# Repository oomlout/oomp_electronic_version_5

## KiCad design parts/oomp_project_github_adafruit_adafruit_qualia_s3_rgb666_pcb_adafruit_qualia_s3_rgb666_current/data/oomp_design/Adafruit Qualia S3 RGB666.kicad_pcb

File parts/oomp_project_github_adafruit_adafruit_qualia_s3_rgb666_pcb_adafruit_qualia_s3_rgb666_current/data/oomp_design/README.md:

# OOMP KiCad design copy

Open `Adafruit Qualia S3 RGB666.kicad_pro` (or the `.kicad_pcb` / `.kicad_sch`) in KiCad. Local OOMP libraries are under `libraries/`. Original inputs are preserved in [../original/](../original/).

Only verified unchanged installed KiCad defaults were renamed. Modified, custom, unmatched and unavailable items remain unchanged. Soldering variants are never swapped during conversion. Existing pad coordinates, nets and UUIDs are preserved.

See [conversion_report.yaml](conversion_report.yaml) for every conversion and skip. Copy this directory before editing; regeneration refuses to overwrite edited design files.

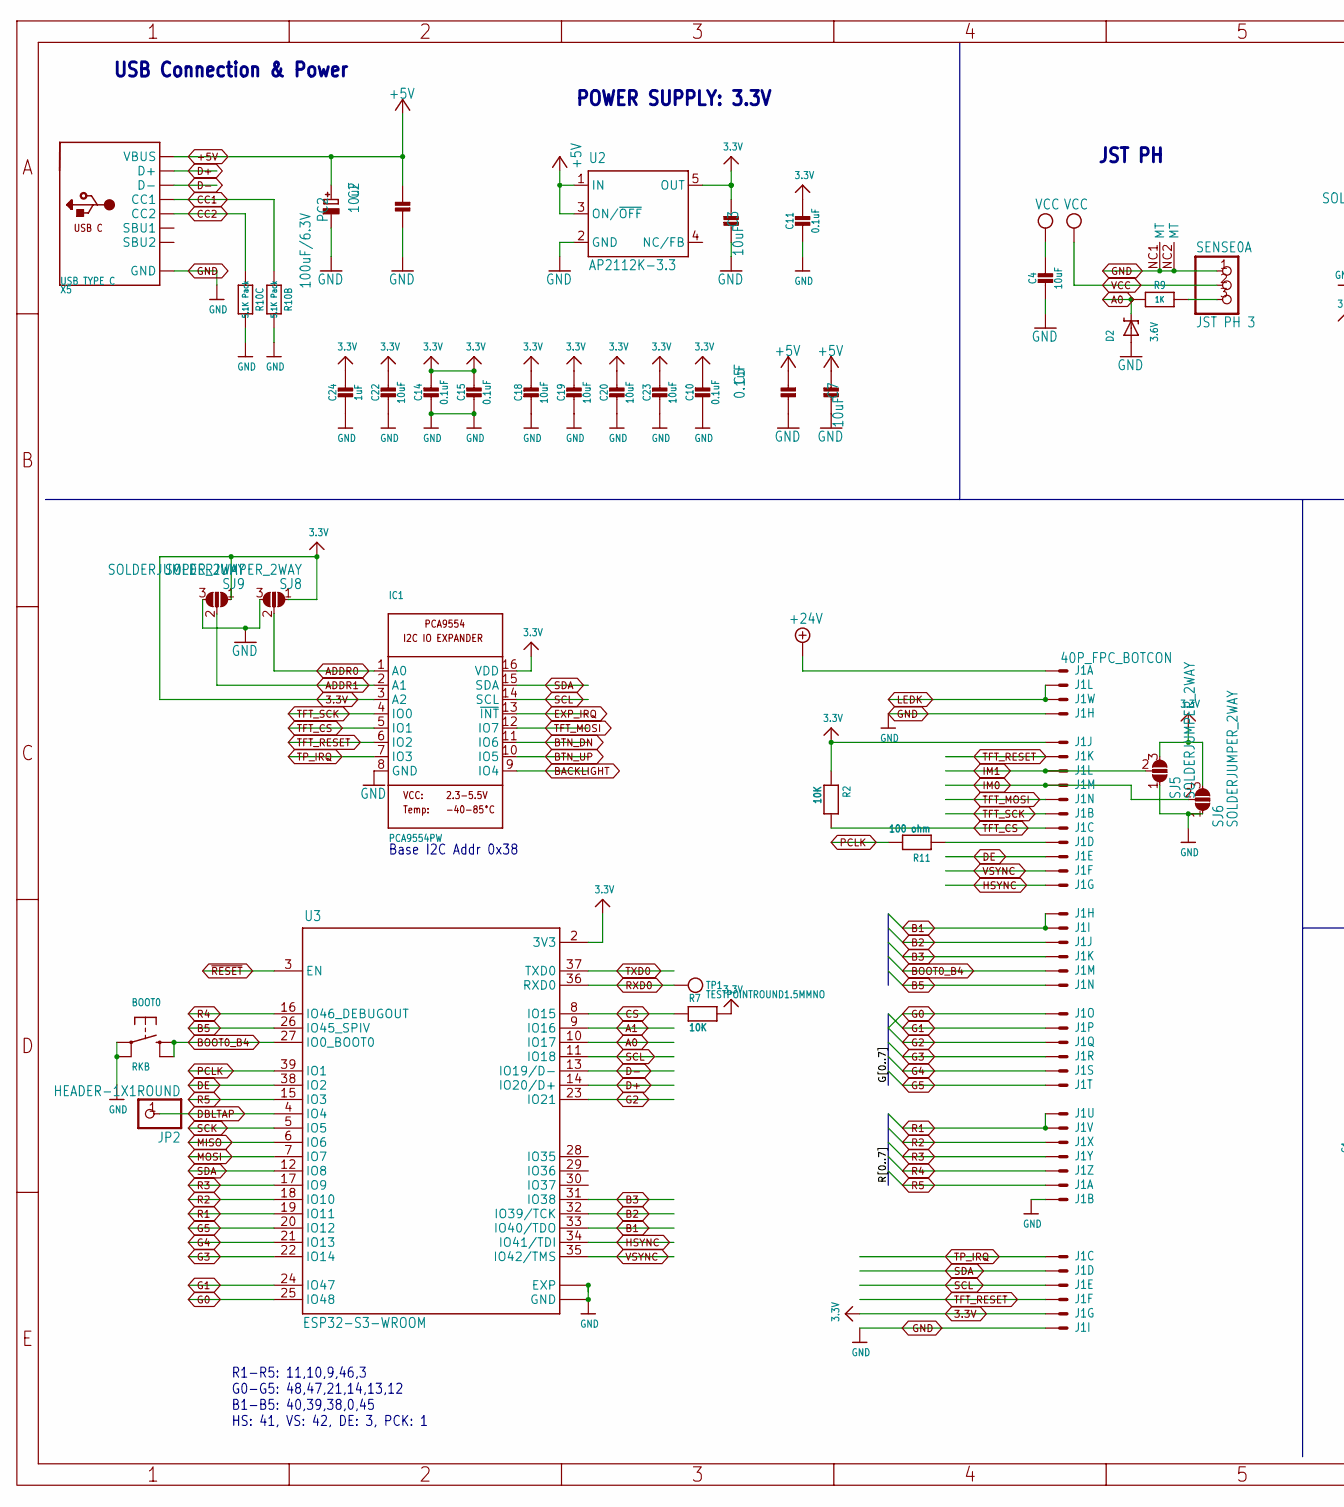
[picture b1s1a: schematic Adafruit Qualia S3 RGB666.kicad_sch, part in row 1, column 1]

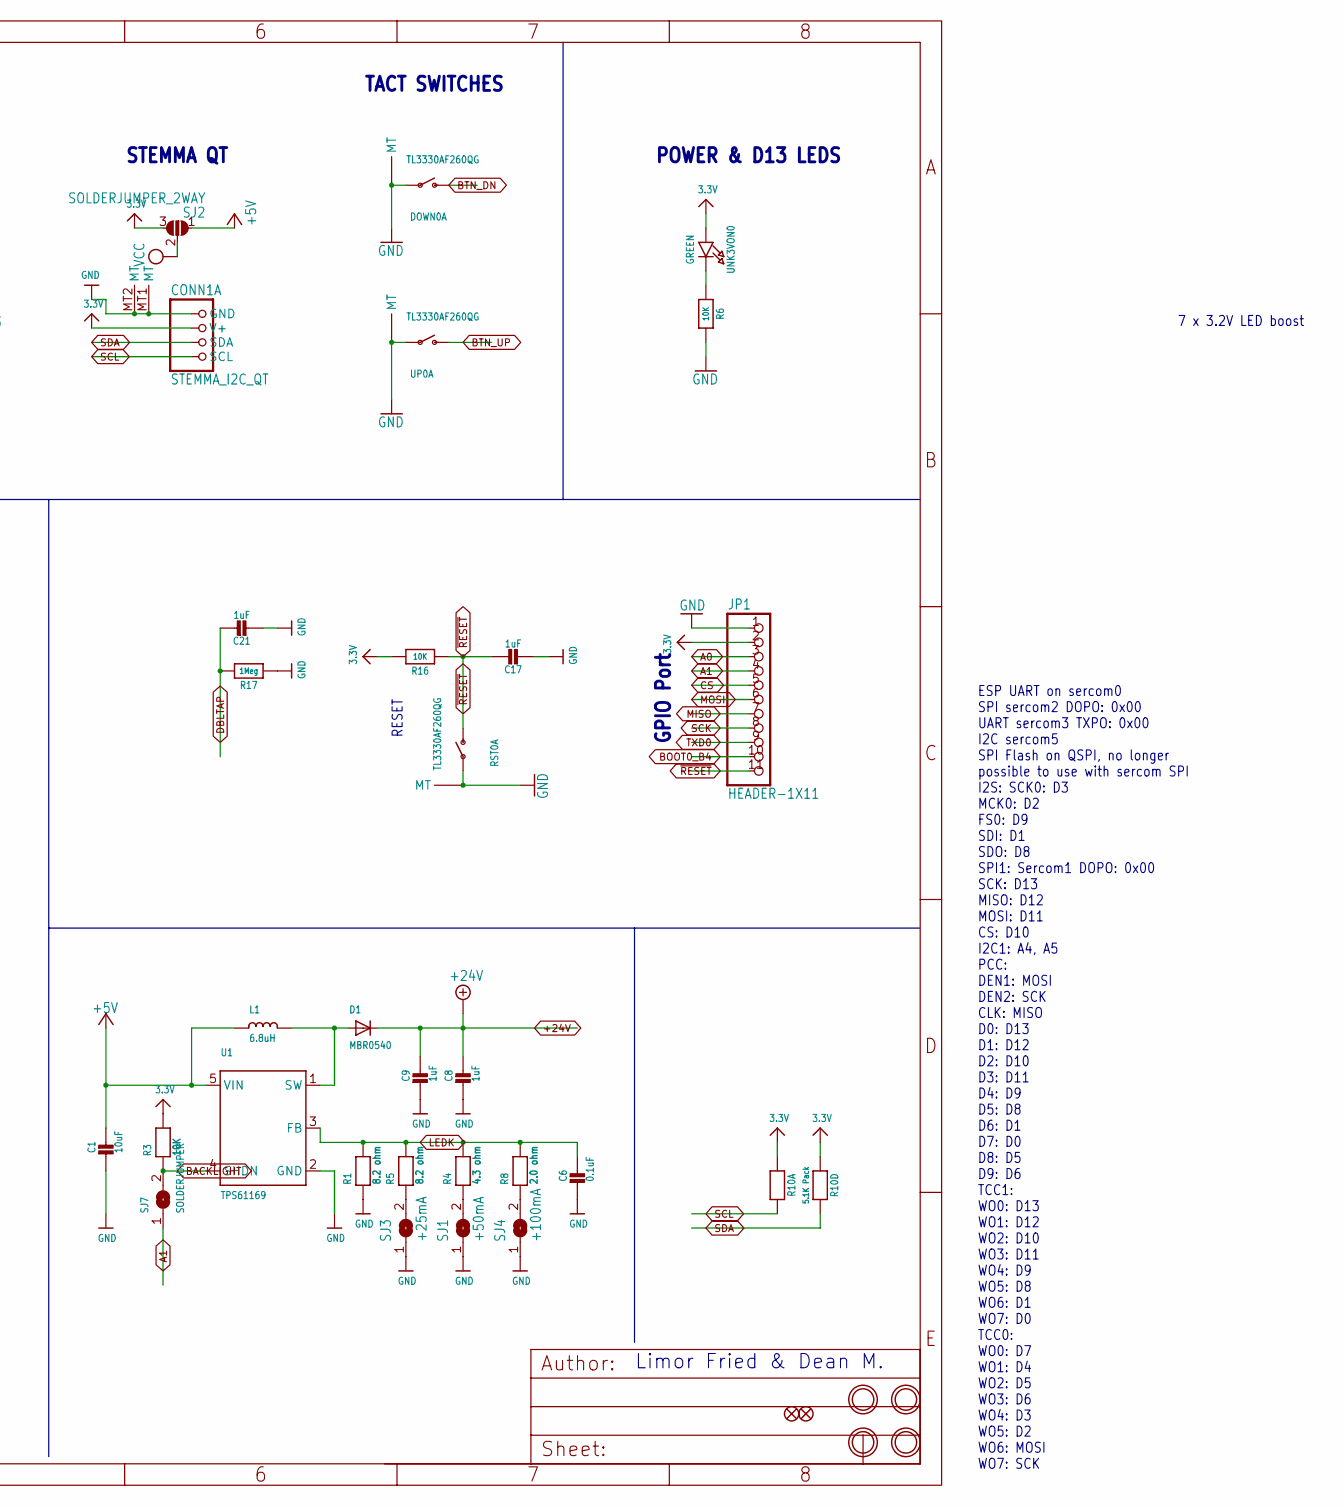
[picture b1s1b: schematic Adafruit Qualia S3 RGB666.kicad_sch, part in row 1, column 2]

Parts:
BOOT0: RKB; BTN_RKB2_4.6X2.8
C1, C2, C3, C4, C7, C18, C19, C20, C22, C23: 10uF; 0805-NO
C5, C6, C10, C11, C14, C15: 0.1uF; 0603-NO
C8, C9, C17, C21, C24: 1uF; 0603-NO
CONN1: STEMMA_I2C_QT; JST_SH4; LCSC C2845363
D1: MBR0540; SOD-123
D2: 3.6V; SOD-323
DOWN0: TL3330AF260QG; SPST_TACTILE_RA; LCSC C778159
FID1, FID2: FIDUCIAL_1MM
IC1: PCA9554PW; TSSOP16
J1: 40P_FPC_BOTCON; FPC_40
JP1: HEADER-1X11; 1X11_ROUND
JP2: HEADER-1X1ROUND; 1X01_ROUND
L1: 6.8uH; INDUCTOR_5X5MM_NR5040_NOTHERMALS
PC2: 100uF/6.3V; PANASONIC_D
R1, R5: 8.2 ohm; 0603-NO
R2, R3, R6, R7, R16: 10K; 0603-NO
R4: 4.3 ohm; 0603-NO
R8: 2.0 ohm; 0603-NO
R9: 1K; 0603-NO
R10: 5.1K Pack; RESPACK_4X0603
R11: 100 ohm; 0603-NO
R17: 1Meg; 0603-NO
RST0: TL3330AF260QG; SPST_TACTILE_RA; LCSC C778159
SENSE0: JST PH 3; JSTPH3
SJ1: +50mA; SOLDERJUMPER_ARROW_NOPASTE
SJ2, SJ5, SJ6, SJ8, SJ9: SOLDERJUMPER_2WAY; SOLDERJUMPER_2WAY_OPEN_NOPASTE
SJ3: +25mA; SOLDERJUMPER_ARROW_NOPASTE
SJ4: +100mA; SOLDERJUMPER_ARROW_NOPASTE
SJ7: SOLDERJUMPER; SOLDERJUMPER_ARROW_NOPASTE
TP1: TESTPOINTROUND1.5MMNO; TESTPOINT_ROUND_1.5MM_NO
U1: TPS61169; SC70-5
U2: AP2112K-3.3; SOT23-DBV
U3: ESP32-S3-WROOM; S3-WROOM32
U$14, U$19, U$22, U$24: MOUNTINGHOLE2.5; MOUNTINGHOLE_2.5_PLATED
UNK3VON0: GREEN; CHIPLED_0603_NOOUTLINE
UP0: TL3330AF260QG; SPST_TACTILE_RA; LCSC C778159
X5: USB TYPE C; USB_C_CUSB31-CFM2AX-01-X; LCSC C165948

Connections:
3.3V: C3.2, C10.2, C11.2, C14.2, C15.2, C18.1, C19.1, C20.1, C22.1, C23.1, C24.1, CONN1.2 (V+), IC1.3 (A2), IC1.16 (VDD), J1.5 (MS), J1.39 (MS), JP1.2, R2.1, R3.2, R7.2, R10.1, R10.4 (1), R16.2, SJ2.3, SJ5.3, SJ6.3, SJ8.1, SJ9.1, U2.5 (OUT), U3.2 (3V3), UNK3VON0.A
+5V: C1.1, C2.2, C5.2, C7.2, L1.P$1 (1), PC2.+, SJ2.1, U1.5 (VIN), U2.1 (IN), U2.3 (ON/~OFF), X5.A4B9 (VBUS), X5.B4A9 (VBUS)
+24V: C8.1, C9.1, D1.C, J1.1 (MSV)
A0: D2.C, JP1.3, R9.2, U3.10 (IO17)
A0_JST: R9.1, SENSE0.3
A1: JP1.4, SJ7.1, U3.9 (IO16)
ADDR0: IC1.1 (A0), SJ8.2
ADDR1: IC1.2 (A1), SJ9.2
B1: J1.16 (MS), J1.17 (MS), U3.33 (IO40/TDO)
B2: J1.18 (MS), U3.32 (IO39/TCK)
B3: J1.19 (MS), U3.31 (IO38)
B5: J1.21 (MS), U3.26 (IO45_SPIV)
BACKLIGHT: IC1.9 (IO4), R3.1, SJ7.2, U1.4 (SHDN)
BOOT0_B4: BOOT0.B (S), BOOT0.B' (S1), J1.20 (MS), JP1.10, U3.27 (IO0_BOOT0)
BTN_DN: DOWN0.2 (S), IC1.11 (IO6)
BTN_UP: IC1.10 (IO5), UP0.2 (S)
CC1: R10.2 (1), X5.A5 (CC1)
CC2: R10.3 (1), X5.B5 (CC2)
CS: JP1.5, R7.1, U3.8 (IO15)
D+: U3.14 (IO20/D+), X5.A6 (D+), X5.B6 (D+)
D-: U3.13 (IO19/D-), X5.A7 (D-), X5.B7 (D-)
DBLTAP: C21.1, JP2.1, R17.2, U3.4 (IO4)
DE: J1.13 (MS), U3.38 (IO2)
EXP_IRQ: IC1.13 (~INT)
G0: J1.22 (MS), U3.25 (IO48)
G1: J1.23 (MS), U3.24 (IO47)
G2: J1.24 (MS), U3.23 (IO21)
G3: J1.25 (MS), U3.22 (IO14)
G4: J1.26 (MS), U3.21 (IO13)
G5: J1.27 (MS), U3.20 (IO12)
GND: BOOT0.A, BOOT0.A' (P1), C1.2, C2.1, C3.1, C4.2, C5.1, C6.2, C7.1, C8.2, C9.2, C10.1, C11.1, C14.1, C15.1, C17.2, C18.2, C19.2, C20.2, C21.2, C22.2, C23.2, C24.2, CONN1.1 (GND), CONN1.MT1 (MT), CONN1.MT2 (MT), D2.A, DOWN0.1, DOWN0.MT1 (MT), DOWN0.MT2 (MT), IC1.8 (GND), J1.4 (MS), J1.34 (MS), J1.40 (MS), JP1.1, PC2.-, R1.1, R6.2, R10.6 (2), R10.7 (2), R17.1, RST0.1, RST0.MT1 (MT), RST0.MT2 (MT), SENSE0.1, SENSE0.NC1 (MT), SENSE0.NC2 (MT), SJ1.1, SJ3.1, SJ4.1, SJ5.1, SJ6.1, SJ8.3, SJ9.3, U1.2 (GND), U2.2 (GND), U3.1 (GND), U3.40 (GND), U3.P$2 (EXP), U3.P$3 (EXP), U3.P$4 (EXP), U3.P$5 (EXP), U3.P$6 (EXP), U3.P$7 (EXP), U3.P$8 (EXP), U3.P$9 (EXP), U3.P$10 (EXP), UP0.1, UP0.MT1 (MT), UP0.MT2 (MT), X5.A1B12 (GND), X5.B1A12 (GND)
HSYNC: J1.15 (MS), U3.34 (IO41/TDI)
IM0: J1.8 (MS), SJ6.2
IM1: J1.7 (MS), SJ5.2
LEDK: C6.1, J1.2 (MS), J1.3 (MS), R1.2, R4.2, R5.2, R8.2, U1.3 (FB)
MISO: JP1.7, U3.6 (IO6)
MOSI: JP1.6, U3.7 (IO7)
unnamed: R6.1, UNK3VON0.C
unnamed: R4.1, SJ1.2
unnamed: J1.12 (MS), R11.1
unnamed: D1.A, L1.P$2 (2), U1.1 (SW)
unnamed: R5.1, SJ3.2
unnamed: R8.1, SJ4.2
PCLK: R11.2, U3.39 (IO1)
R1: J1.28 (MS), J1.29 (MS), U3.19 (IO11)
R2: J1.30 (MS), U3.18 (IO10)
R3: J1.31 (MS), U3.17 (IO9)
R4: J1.32 (MS), U3.16 (IO46_DEBUGOUT)
R5: J1.33 (MS), U3.15 (IO3)
RXD0: TP1.P$1, U3.36 (RXD0)
SCK: JP1.8, U3.5 (IO5)
SCL: CONN1.4 (SCL), IC1.14 (SCL), J1.37 (MS), R10.8 (2), U3.11 (IO18)
SDA: CONN1.3 (SDA), IC1.15 (SDA), J1.36 (MS), R10.5 (2), U3.12 (IO8)
TFT_CS: IC1.5 (IO1), J1.11 (MS), R2.2
TFT_MOSI: IC1.12 (IO7), J1.9 (MS)
TFT_RESET: IC1.6 (IO2), J1.6 (MS), J1.38 (MS)
TFT_SCK: IC1.4 (IO0), J1.10 (MS)
TP_IRQ: IC1.7 (IO3), J1.35 (MS)
TXD0: JP1.9, U3.37 (TXD0)
VCC: C4.1, SENSE0.2, SJ2.2
VSYNC: J1.14 (MS), U3.35 (IO42/TMS)
~RESET: C17.1, JP1.11, R16.1, RST0.2 (S), U3.3 (EN)

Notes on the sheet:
JST PH
7 x 3.2V LED boost
POWER SUPPLY: 3.3V
ESP UART on sercom0 SPI sercom2 DOPO: 0x00 UART sercom3 TXPO: 0x00 I2C sercom5 SPI Flash on QSPI, no longer possible to use with sercom SPI I2S: SCK0: D3 MCK0: D2 FS0: D9 SDI: D1 SDO: D8 SPI1: Sercom1 DOPO: 0x00 SCK: D13 MISO: D12 MOSI: D11 CS: D10 I2C1: A4, A5 PCC: DEN1: MOSI DEN2: SCK CLK: MISO D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
TACT SWITCHES
GPIO Port
Limor Fried & Dean M.
USB Connection & Power
R1-R5: 11,10,9,46,3 G0-G5: 48,47,21,14,13,12 B1-B5: 40,39,38,0,45 HS: 41, VS: 42, DE: 3, PCK: 1
Base I2C Addr 0x38
POWER & D13 LEDS
RESET
STEMMA QT

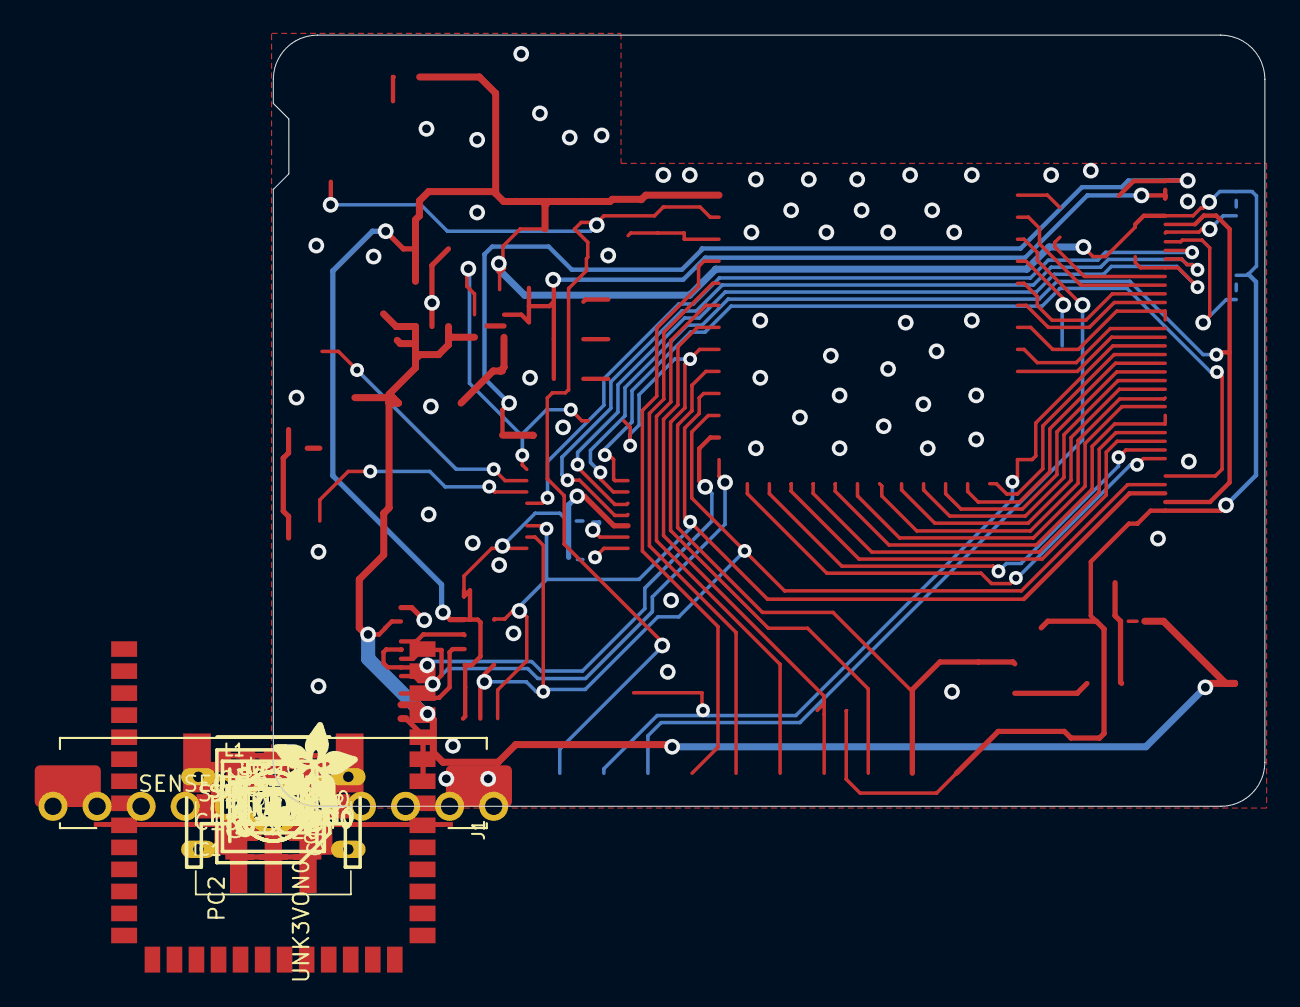
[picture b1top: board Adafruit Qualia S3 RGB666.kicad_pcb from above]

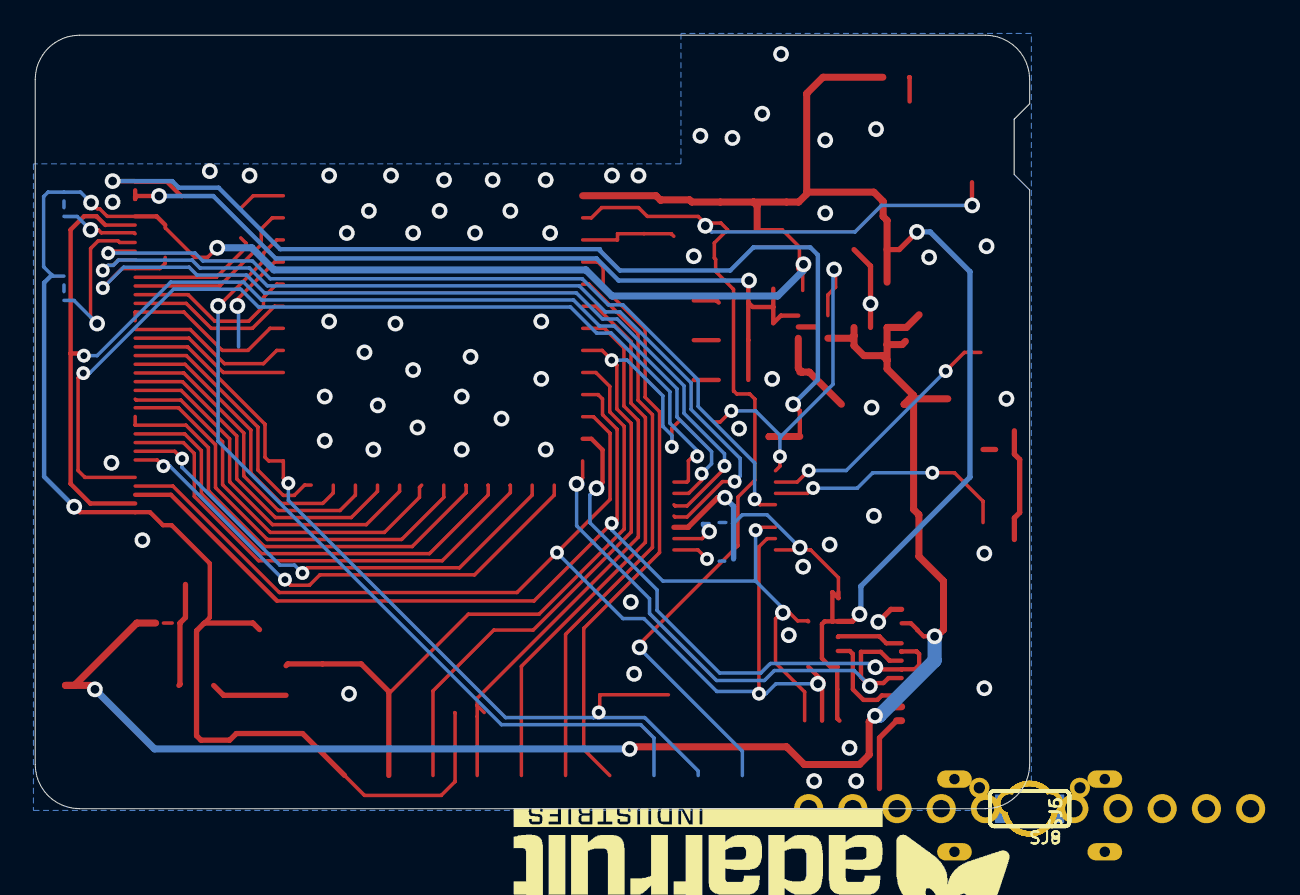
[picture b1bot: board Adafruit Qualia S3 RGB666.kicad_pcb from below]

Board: 2 copper layers, 57.1 x 44.5 mm, 112 parts (19 on the bottom side), 61 nets.

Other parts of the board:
PLABEL0: PLABEL0
PLABEL1: PLABEL1
PLABEL2: PLABEL2
PLABEL3: PLABEL3
PLABEL4: PLABEL4
PLABEL5: PLABEL5
PLABEL6: PLABEL6
PLABEL7: PLABEL7
PLABEL8: PLABEL8
PLABEL9: PLABEL9
PLABEL10: PLABEL10
PLABEL11: PLABEL11
PLABEL12: PLABEL12
PLABEL13: PLABEL13
PLABEL14: PLABEL14
PLABEL15: PLABEL15
PLABEL16: PLABEL16
PLABEL17: PLABEL17
PLABEL18: PLABEL18
PLABEL19: PLABEL19
PLABEL20: PLABEL20
PLABEL21: PLABEL21
PLABEL22: PLABEL22
PLABEL23: PLABEL23
PLABEL24: PLABEL24
PLABEL25: PLABEL25
PLABEL26: PLABEL26
PLABEL27: PLABEL27
PLABEL28: PLABEL28
PLABEL29: PLABEL29
PLABEL30: PLABEL30
PLABEL31: PLABEL31
PLABEL32: PLABEL32
PLABEL33: PLABEL33
PLABEL34: PLABEL34
PLABEL35: PLABEL35
PLABEL36: PLABEL36
PLABEL37: PLABEL37
PLABEL38: PLABEL38
PLABEL39: PLABEL39
U$44: PCBFEAT-REV-040
U$46: ADAFRUIT_5MM
U$49: ADAFRUIT_TEXT_30MM

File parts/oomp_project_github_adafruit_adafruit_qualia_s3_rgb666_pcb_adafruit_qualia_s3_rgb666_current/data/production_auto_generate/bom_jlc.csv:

Comment,Designator,Footprint,LCSC Part #
,JP2,Adafruit Qualia S3 RGB666-import-fps:1X01_ROUND,C7501259
,JP1,Adafruit Qualia S3 RGB666-import-fps:1X11_ROUND,C2894934
,U$46,Adafruit Qualia S3 RGB666-import-fps:ADAFRUIT_5MM,
,U$49,Adafruit Qualia S3 RGB666-import-fps:ADAFRUIT_TEXT_30MM,
,U$44,Adafruit Qualia S3 RGB666-import-fps:PCBFEAT-REV-040,
,PLABEL0,Adafruit Qualia S3 RGB666-import-fps:PLABEL0,
,PLABEL1,Adafruit Qualia S3 RGB666-import-fps:PLABEL1,
,PLABEL10,Adafruit Qualia S3 RGB666-import-fps:PLABEL10,
,PLABEL11,Adafruit Qualia S3 RGB666-import-fps:PLABEL11,
,PLABEL12,Adafruit Qualia S3 RGB666-import-fps:PLABEL12,
,PLABEL13,Adafruit Qualia S3 RGB666-import-fps:PLABEL13,
,PLABEL14,Adafruit Qualia S3 RGB666-import-fps:PLABEL14,
,PLABEL15,Adafruit Qualia S3 RGB666-import-fps:PLABEL15,
,PLABEL16,Adafruit Qualia S3 RGB666-import-fps:PLABEL16,
,PLABEL17,Adafruit Qualia S3 RGB666-import-fps:PLABEL17,
,PLABEL18,Adafruit Qualia S3 RGB666-import-fps:PLABEL18,
,PLABEL19,Adafruit Qualia S3 RGB666-import-fps:PLABEL19,
,PLABEL2,Adafruit Qualia S3 RGB666-import-fps:PLABEL2,
,PLABEL20,Adafruit Qualia S3 RGB666-import-fps:PLABEL20,
,PLABEL21,Adafruit Qualia S3 RGB666-import-fps:PLABEL21,
,PLABEL22,Adafruit Qualia S3 RGB666-import-fps:PLABEL22,
,PLABEL23,Adafruit Qualia S3 RGB666-import-fps:PLABEL23,
,PLABEL24,Adafruit Qualia S3 RGB666-import-fps:PLABEL24,
,PLABEL25,Adafruit Qualia S3 RGB666-import-fps:PLABEL25,
,PLABEL26,Adafruit Qualia S3 RGB666-import-fps:PLABEL26,
,PLABEL27,Adafruit Qualia S3 RGB666-import-fps:PLABEL27,
,PLABEL28,Adafruit Qualia S3 RGB666-import-fps:PLABEL28,
,PLABEL29,Adafruit Qualia S3 RGB666-import-fps:PLABEL29,
,PLABEL3,Adafruit Qualia S3 RGB666-import-fps:PLABEL3,
,PLABEL30,Adafruit Qualia S3 RGB666-import-fps:PLABEL30,
,PLABEL31,Adafruit Qualia S3 RGB666-import-fps:PLABEL31,
,PLABEL32,Adafruit Qualia S3 RGB666-import-fps:PLABEL32,
,PLABEL33,Adafruit Qualia S3 RGB666-import-fps:PLABEL33,
,PLABEL34,Adafruit Qualia S3 RGB666-import-fps:PLABEL34,
,PLABEL35,Adafruit Qualia S3 RGB666-import-fps:PLABEL35,
,PLABEL36,Adafruit Qualia S3 RGB666-import-fps:PLABEL36,
,PLABEL37,Adafruit Qualia S3 RGB666-import-fps:PLABEL37,
,PLABEL38,Adafruit Qualia S3 RGB666-import-fps:PLABEL38,
,PLABEL39,Adafruit Qualia S3 RGB666-import-fps:PLABEL39,
,PLABEL4,Adafruit Qualia S3 RGB666-import-fps:PLABEL4,
,PLABEL5,Adafruit Qualia S3 RGB666-import-fps:PLABEL5,
,PLABEL6,Adafruit Qualia S3 RGB666-import-fps:PLABEL6,
,PLABEL7,Adafruit Qualia S3 RGB666-import-fps:PLABEL7,
,PLABEL8,Adafruit Qualia S3 RGB666-import-fps:PLABEL8,
,PLABEL9,Adafruit Qualia S3 RGB666-import-fps:PLABEL9,
,TP1,Adafruit Qualia S3 RGB666-import-fps:TESTPOINT_ROUND_1.5MM_NO,
0.1uF,"C5,C6,C10,C11,C14,C15",Adafruit Qualia S3 RGB666-import-fps:0603-NO,C14663
100 ohm,R11,Adafruit Qualia S3 RGB666-import-fps:0603-NO,C22775
100uF/6.3V,PC2,Adafruit Qualia S3 RGB666-import-fps:PANASONIC_D,
10K,"R2,R3,R6,R7,R16",Adafruit Qualia S3 RGB666-import-fps:0603-NO,C98220
10uF,"C1,C2,C3,C4,C7,C18,C19,C20,C22,C23",Adafruit Qualia S3 RGB666-import-fps:0805-NO,
1K,R9,Adafruit Qualia S3 RGB666-import-fps:0603-NO,C2907002
1Meg,R17,Adafruit Qualia S3 RGB666-import-fps:0603-NO,C2907003
1uF,"C8,C9,C17,C21,C24",Adafruit Qualia S3 RGB666-import-fps:0603-NO,C5673
2.0 ohm,R8,Adafruit Qualia S3 RGB666-import-fps:0603-NO,
3.6V,D2,Adafruit Qualia S3 RGB666-import-fps:SOD-323,
4.3 ohm,R4,Adafruit Qualia S3 RGB666-import-fps:0603-NO,
40P_FPC_BOTCON,J1,Adafruit Qualia S3 RGB666-import-fps:FPC_40,
5.1K Pack,R10,Adafruit Qualia S3 RGB666-import-fps:RESPACK_4X0603,C23186
6.8uH,L1,Adafruit Qualia S3 RGB666-import-fps:INDUCTOR_5X5MM_NR5040_NOTHERMALS,
8.2 ohm,"R1,R5",Adafruit Qualia S3 RGB666-import-fps:0603-NO,
AP2112K-3.3,U2,Adafruit Qualia S3 RGB666-import-fps:SOT23-DBV,
ESP32-S3-WROOM,U3,Adafruit Qualia S3 RGB666-import-fps:S3-WROOM32,
GREEN,UNK3VON0,Adafruit Qualia S3 RGB666-import-fps:CHIPLED_0603_NOOUTLINE,
JST PH 3,SENSE0,Adafruit Qualia S3 RGB666-import-fps:JSTPH3,
MBR0540,D1,Adafruit Qualia S3 RGB666-import-fps:SOD-123,
PCA9554PW,IC1,Adafruit Qualia S3 RGB666-import-fps:TSSOP16,
RKB,BOOT0,Adafruit Qualia S3 RGB666-import-fps:BTN_RKB2_4.6X2.8,
STEMMA_I2C_QT,CONN1,Adafruit Qualia S3 RGB666-import-fps:JST_SH4,C160404
TL3330AF260QG,"DOWN0,RST0,UP0",Adafruit Qualia S3 RGB666-import-fps:SPST_TACTILE_RA,
TPS61169,U1,Adafruit Qualia S3 RGB666-import-fps:SC70-5,
USB TYPE C,X5,Adafruit Qualia S3 RGB666-import-fps:USB_C_CUSB31-CFM2AX-01-X,

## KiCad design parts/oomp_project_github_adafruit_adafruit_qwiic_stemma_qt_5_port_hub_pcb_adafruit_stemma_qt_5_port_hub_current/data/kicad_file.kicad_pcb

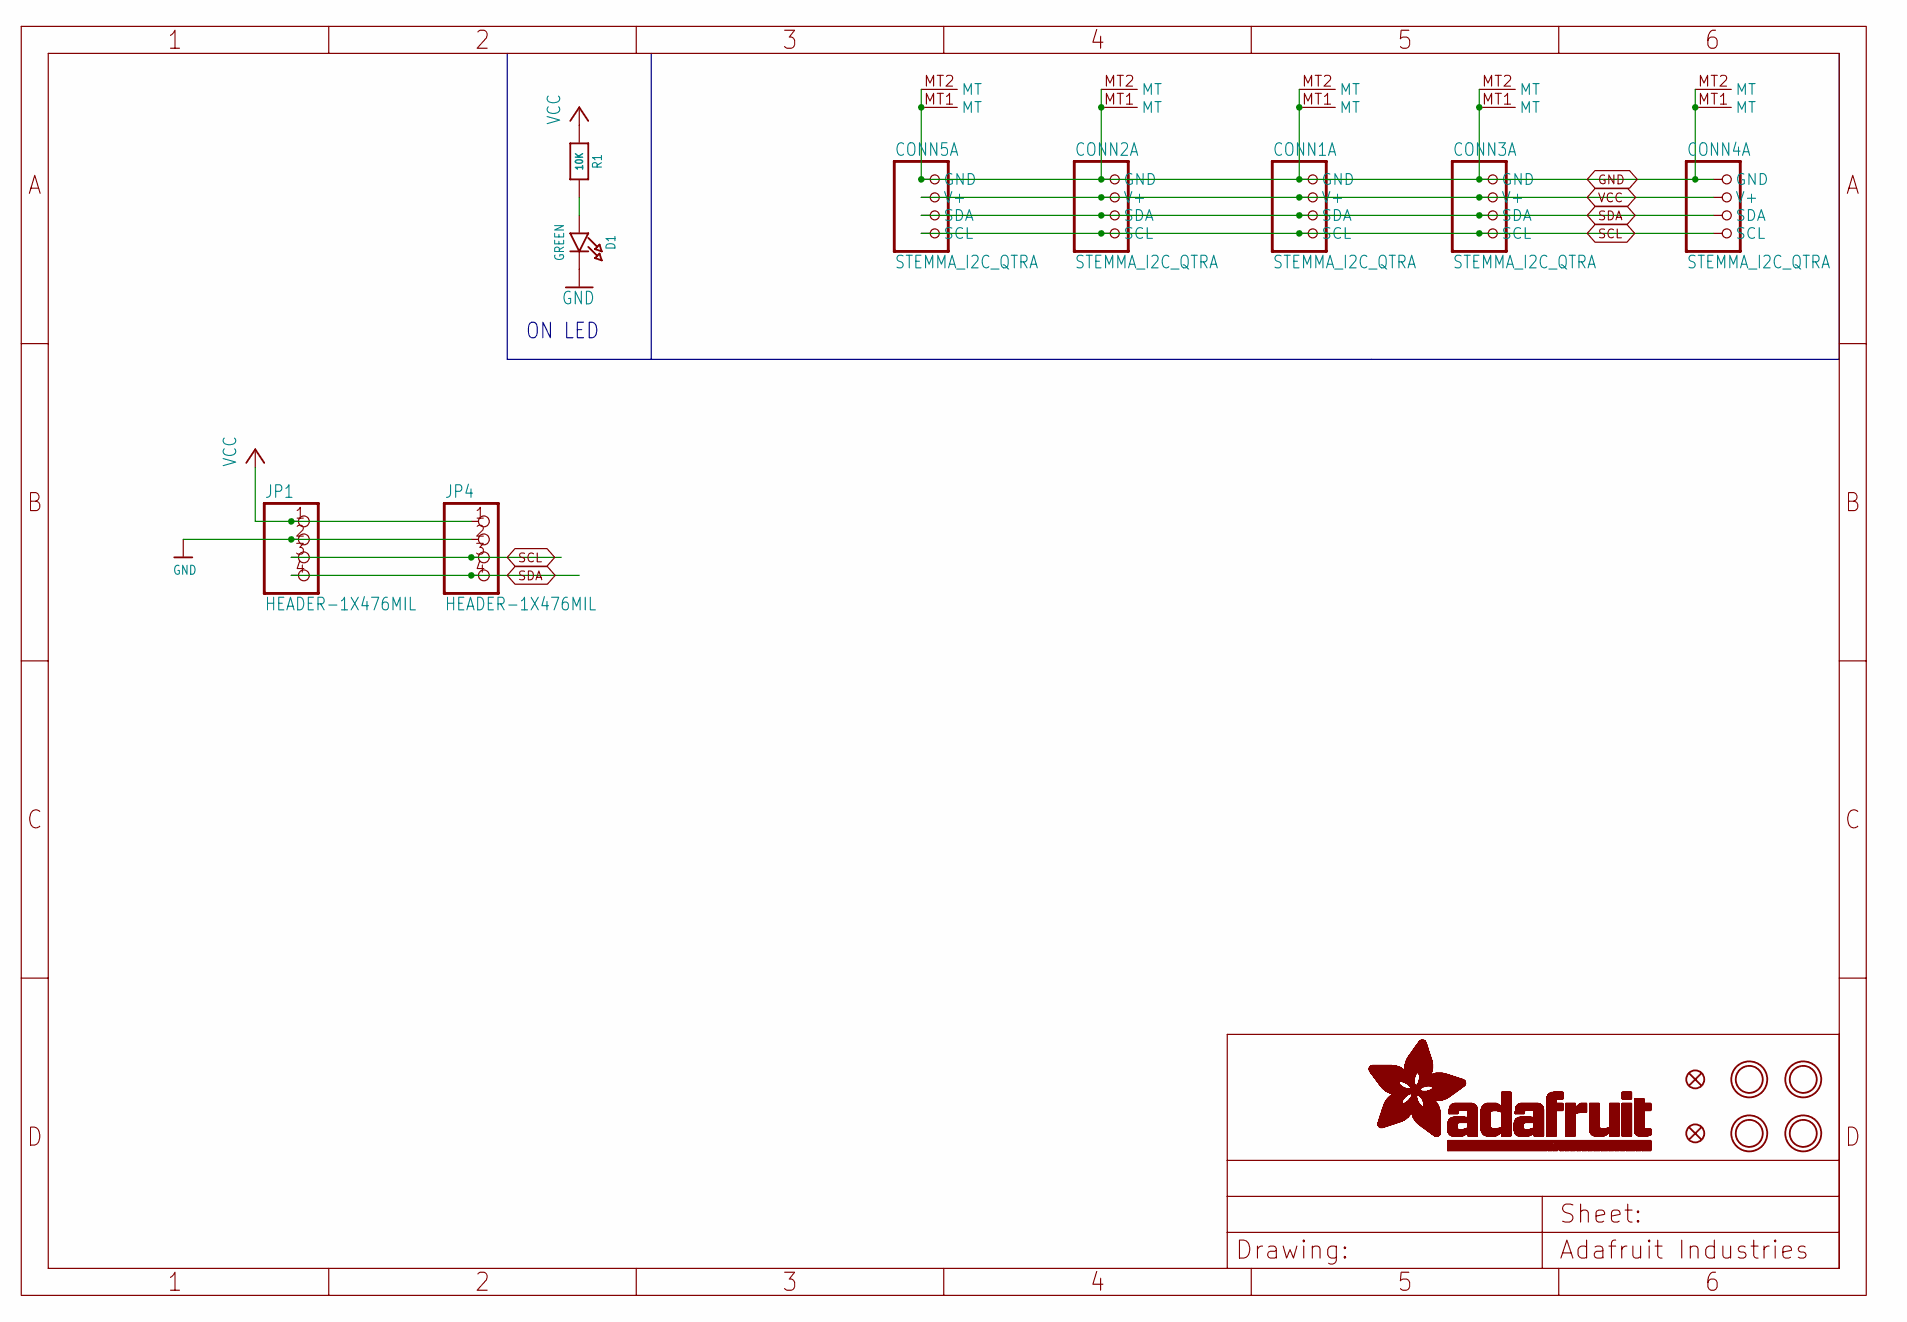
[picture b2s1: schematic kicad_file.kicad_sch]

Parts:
CONN1, CONN2, CONN3, CONN4, CONN5: STEMMA_I2C_QTRA; JST_SH4_RA; LCSC C145961
D1: GREEN; CHIPLED_0603_NOOUTLINE; JLC_ROTATION 270
FID3, FID4: FIDUCIAL_1MM
JP1, JP4: HEADER-1X476MIL; 1X04_ROUND_76
R1: 10K; 0603-NO
U$1, U$17, U$19, U$21: MOUNTINGHOLE2.5; MOUNTINGHOLE_2.5_PLATED

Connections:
GND: CONN1.1 (GND), CONN1.MT1 (MT), CONN1.MT2 (MT), CONN2.1 (GND), CONN2.MT1 (MT), CONN2.MT2 (MT), CONN3.1 (GND), CONN3.MT1 (MT), CONN3.MT2 (MT), CONN4.1 (GND), CONN4.MT1 (MT), CONN4.MT2 (MT), CONN5.1 (GND), CONN5.MT1 (MT), CONN5.MT2 (MT), D1.C, JP1.2, JP4.2
unnamed: D1.A, R1.2
SCL: CONN1.4 (SCL), CONN2.4 (SCL), CONN3.4 (SCL), CONN4.4 (SCL), CONN5.4 (SCL), JP1.3, JP4.3
SDA: CONN1.3 (SDA), CONN2.3 (SDA), CONN3.3 (SDA), CONN4.3 (SDA), CONN5.3 (SDA), JP1.4, JP4.4
VCC: CONN1.2 (V+), CONN2.2 (V+), CONN3.2 (V+), CONN4.2 (V+), CONN5.2 (V+), JP1.1, JP4.1, R1.1

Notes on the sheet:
ON LED

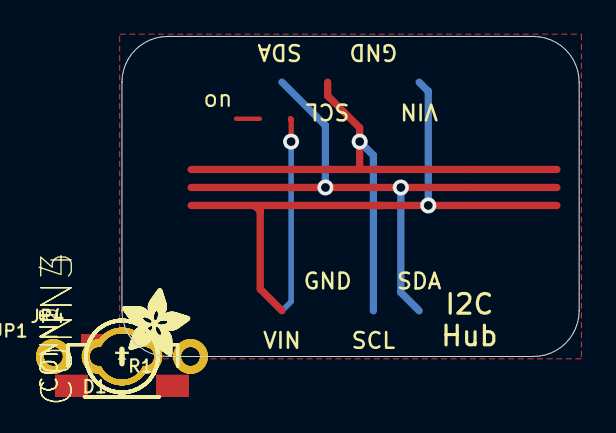
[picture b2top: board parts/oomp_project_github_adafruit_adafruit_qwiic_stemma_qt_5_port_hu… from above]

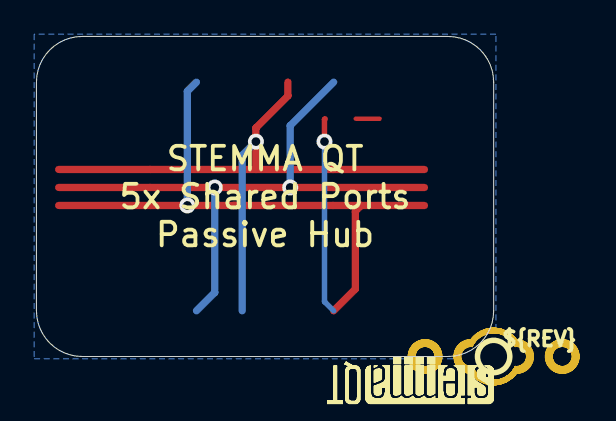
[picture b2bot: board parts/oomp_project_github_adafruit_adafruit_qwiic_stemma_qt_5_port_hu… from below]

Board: 2 copper layers, 25.4 x 17.8 mm, 20 parts (3 on the bottom side), 5 nets.

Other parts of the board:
U$2, U$3: ADAFRUIT_3.5MM
U$25: PCBFEAT-REV-040
U$30, U$31: STEMMAQT

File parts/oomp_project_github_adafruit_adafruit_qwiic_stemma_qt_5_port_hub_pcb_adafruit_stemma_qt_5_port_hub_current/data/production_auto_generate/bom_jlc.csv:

Comment,Designator,Footprint,LCSC Part #
,"JP1,JP4",Adafruit Stemma QT 5 Port Hub-import-fps:1X04_ROUND_76,C42431795
,"U$2,U$3",Adafruit Stemma QT 5 Port Hub-import-fps:ADAFRUIT_3.5MM,
,U$25,Adafruit Stemma QT 5 Port Hub-import-fps:PCBFEAT-REV-040,
,"U$30,U$31",Adafruit Stemma QT 5 Port Hub-import-fps:STEMMAQT,
10K,R1,Adafruit Stemma QT 5 Port Hub-import-fps:0603-NO,C98220
GREEN,D1,Adafruit Stemma QT 5 Port Hub-import-fps:CHIPLED_0603_NOOUTLINE,
STEMMA_I2C_QTRA,"CONN1,CONN2,CONN3,CONN4,CONN5",Adafruit Stemma QT 5 Port Hub-import-fps:JST_SH4_RA,

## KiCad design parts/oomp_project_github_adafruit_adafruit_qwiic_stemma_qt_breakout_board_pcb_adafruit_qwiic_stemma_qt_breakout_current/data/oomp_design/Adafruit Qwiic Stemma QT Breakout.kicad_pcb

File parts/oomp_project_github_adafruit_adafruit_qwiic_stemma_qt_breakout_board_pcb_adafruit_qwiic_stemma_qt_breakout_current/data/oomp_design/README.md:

# OOMP KiCad design copy

Open `Adafruit Qwiic Stemma QT Breakout.kicad_pro` (or the `.kicad_pcb` / `.kicad_sch`) in KiCad. Local OOMP libraries are under `libraries/`. Original inputs are preserved in [../original/](../original/).

Only verified unchanged installed KiCad defaults were renamed. Modified, custom, unmatched and unavailable items remain unchanged. Soldering variants are never swapped during conversion. Existing pad coordinates, nets and UUIDs are preserved.

See [conversion_report.yaml](conversion_report.yaml) for every conversion and skip. Copy this directory before editing; regeneration refuses to overwrite edited design files.

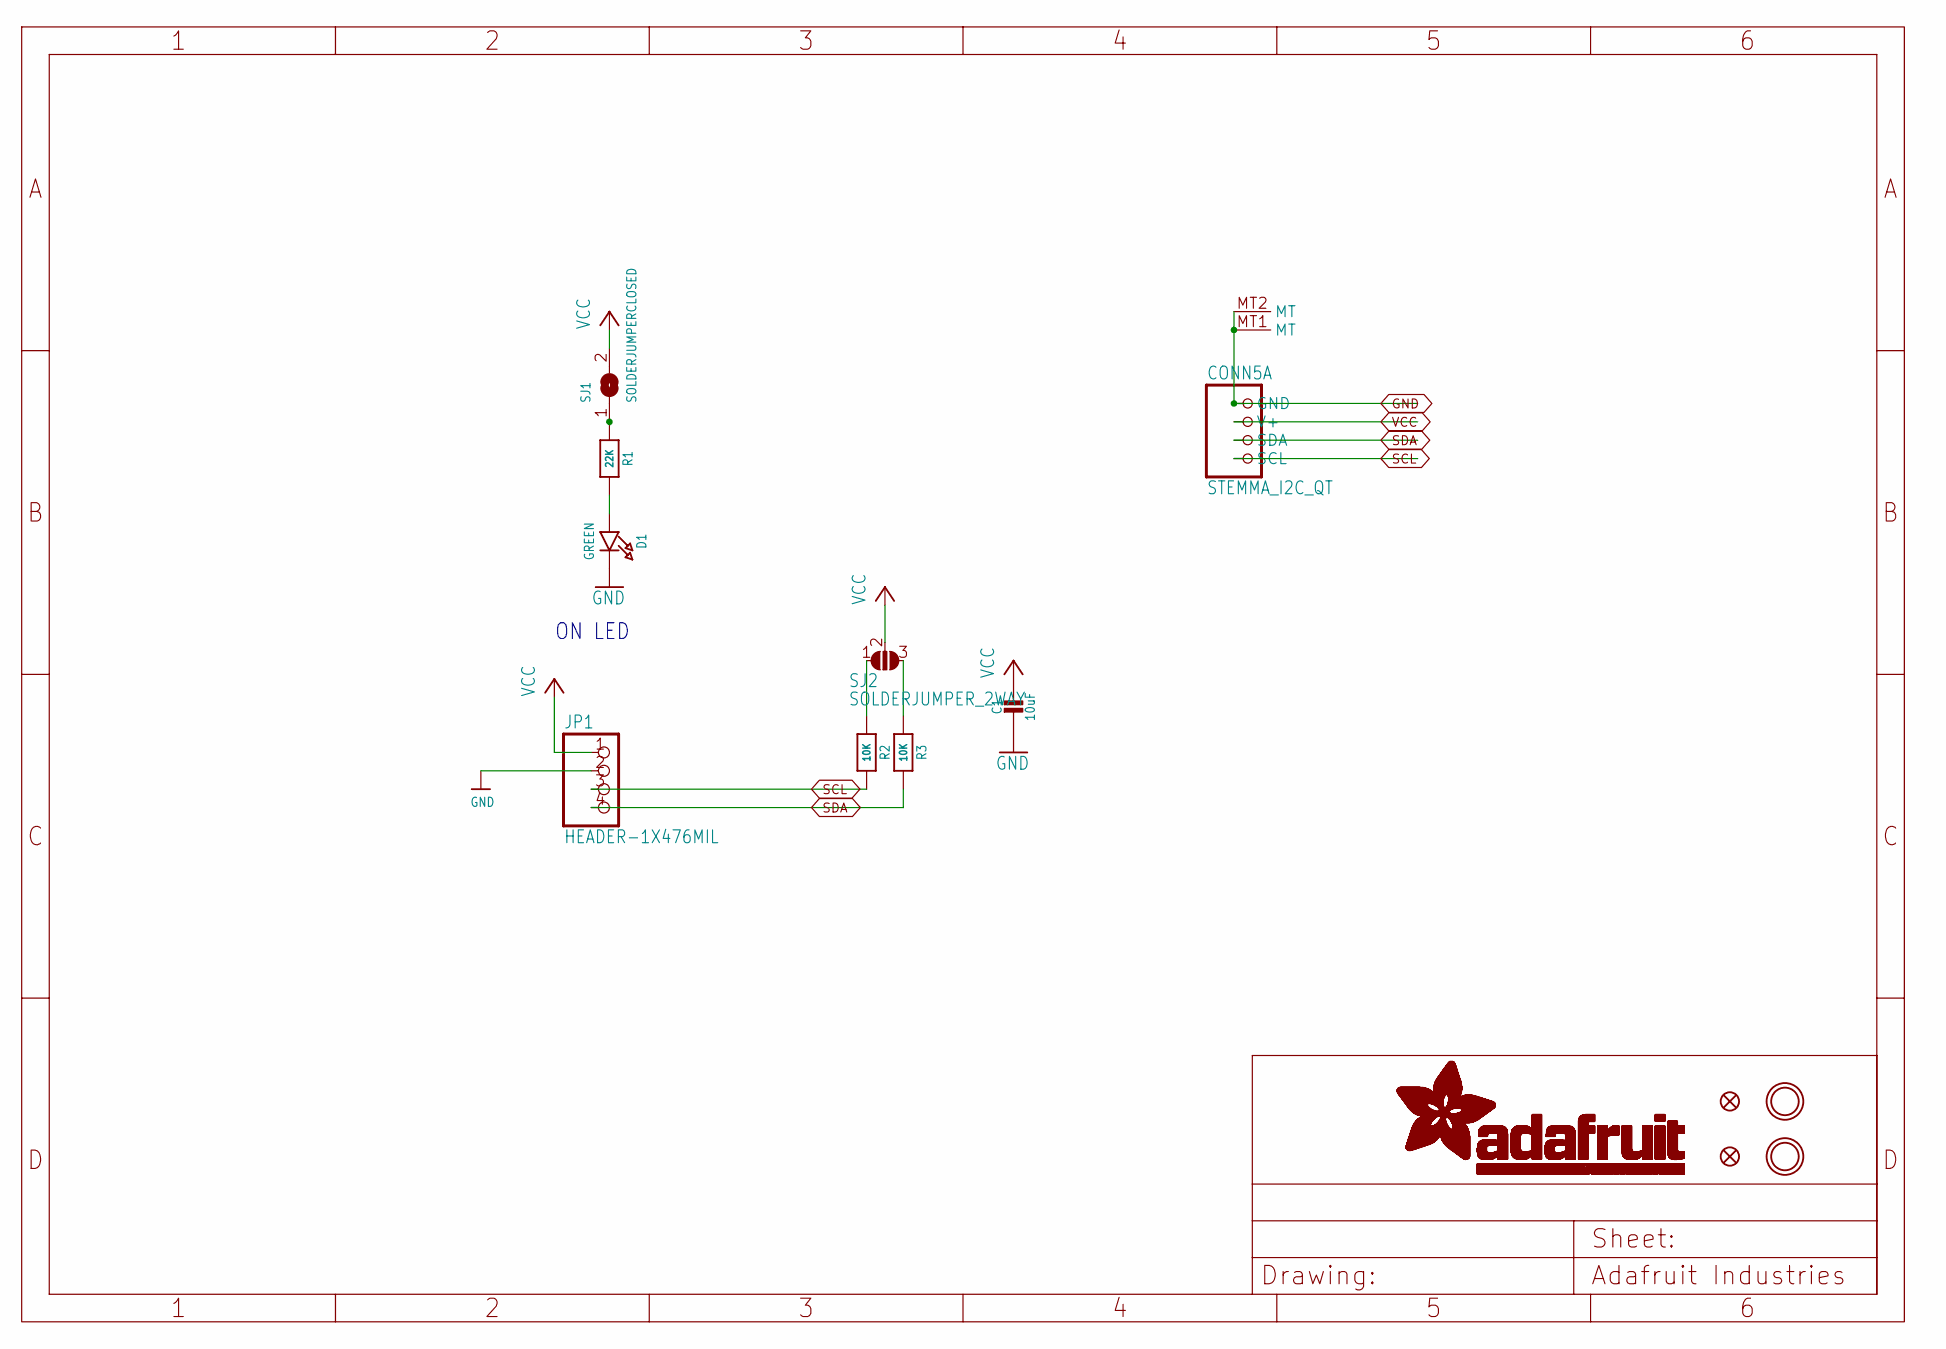
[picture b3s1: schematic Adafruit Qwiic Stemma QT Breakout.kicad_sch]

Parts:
C1: 10uF; 0805-NO
CONN5: STEMMA_I2C_QT; JST_SH4; LCSC C2845363
D1: GREEN; CHIPLED_0603_NOOUTLINE; JLC_ROTATION 270
FID3, FID4: FIDUCIAL_1MM
JP1: HEADER-1X476MIL; 1X04_ROUND_76
R1: 22K; 0603-NO
R2, R3: 10K; 0603-NO
SJ1: SOLDERJUMPERCLOSED; SOLDERJUMPER_CLOSEDWIRE
SJ2: SOLDERJUMPER_2WAY; SOLDERJUMPER_2WAY_OPEN_NOPASTE
U$1, U$17: MOUNTINGHOLE2.5; MOUNTINGHOLE_2.5_PLATED

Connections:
GND: C1.2, CONN5.1 (GND), CONN5.MT1 (MT), CONN5.MT2 (MT), D1.C, JP1.2
unnamed: D1.A, R1.2
unnamed: R1.1, SJ1.1
unnamed: R2.1, SJ2.1
unnamed: R3.1, SJ2.3
SCL: CONN5.4 (SCL), JP1.3, R2.2
SDA: CONN5.3 (SDA), JP1.4, R3.2
VCC: C1.1, CONN5.2 (V+), JP1.1, SJ1.2, SJ2.2

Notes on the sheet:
ON LED

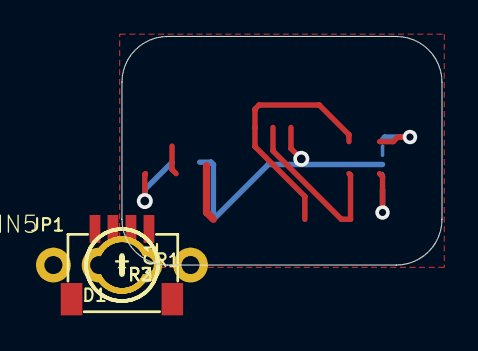
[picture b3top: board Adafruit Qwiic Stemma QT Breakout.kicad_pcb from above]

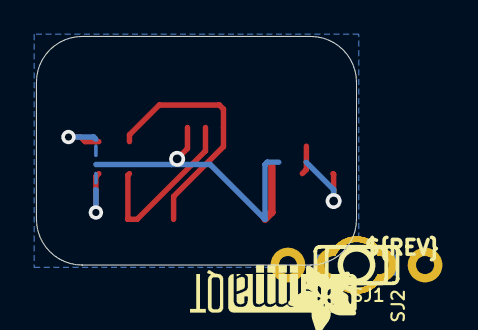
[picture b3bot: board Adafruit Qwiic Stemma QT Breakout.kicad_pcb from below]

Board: 2 copper layers, 17.8 x 12.7 mm, 23 parts (7 on the bottom side), 8 nets.

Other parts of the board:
PLABEL0: PLABEL0
PLABEL1: PLABEL1
PLABEL2: PLABEL2
PLABEL3: PLABEL3
PLABEL4: PLABEL4
PLABEL5: PLABEL5
PLABEL6: PLABEL6
U$2: ADAFRUIT_3.5MM
U$25: PCBFEAT-REV-040
U$31: STEMMAQT

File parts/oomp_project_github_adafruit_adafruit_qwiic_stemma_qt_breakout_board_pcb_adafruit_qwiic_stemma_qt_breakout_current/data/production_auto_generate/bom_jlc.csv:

Comment,Designator,Footprint,LCSC Part #
,JP1,Adafruit Qwiic Stemma QT Breakout-import-fps:1X04_ROUND_76,C42431795
,U$2,Adafruit Qwiic Stemma QT Breakout-import-fps:ADAFRUIT_3.5MM,
,U$25,Adafruit Qwiic Stemma QT Breakout-import-fps:PCBFEAT-REV-040,
,PLABEL0,Adafruit Qwiic Stemma QT Breakout-import-fps:PLABEL0,
,PLABEL1,Adafruit Qwiic Stemma QT Breakout-import-fps:PLABEL1,
,PLABEL2,Adafruit Qwiic Stemma QT Breakout-import-fps:PLABEL2,
,PLABEL3,Adafruit Qwiic Stemma QT Breakout-import-fps:PLABEL3,
,PLABEL4,Adafruit Qwiic Stemma QT Breakout-import-fps:PLABEL4,
,PLABEL5,Adafruit Qwiic Stemma QT Breakout-import-fps:PLABEL5,
,PLABEL6,Adafruit Qwiic Stemma QT Breakout-import-fps:PLABEL6,
,U$31,Adafruit Qwiic Stemma QT Breakout-import-fps:STEMMAQT,
10K,"R2,R3",Adafruit Qwiic Stemma QT Breakout-import-fps:0603-NO,C98220
10uF,C1,Adafruit Qwiic Stemma QT Breakout-import-fps:0805-NO,
22K,R1,Adafruit Qwiic Stemma QT Breakout-import-fps:0603-NO,C31850
GREEN,D1,Adafruit Qwiic Stemma QT Breakout-import-fps:CHIPLED_0603_NOOUTLINE,
STEMMA_I2C_QT,CONN5,Adafruit Qwiic Stemma QT Breakout-import-fps:JST_SH4,C160404
